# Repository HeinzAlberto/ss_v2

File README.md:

# ss_v2
Soldering Station v2 Projekt

Das Soldering Station v2 Projekt basiert auf dem SolderingStation Projekt: https://github.com/ConnyCola/SolderingStation.
Da dieses Projekt nun schon einige Jahre alt ist und mir ein paar kleine Tweeks wie USB-C input oder User-Buttons fehlen, ist dies somit die inoffizielle Fortsetzung.
Der Code basiert maßgebend auf dem des Originalprojekts. 
Hinzugefügt wurde:
- User-Buttons Funktionen (speichern, abrufen und löschen von selbst festgelegten Temperaturwerten)
- Automatisches Standby, wenn PWM über gewisse Zeit einen Wert nicht überschreitet
- Menü, um obriges einzustellen

Die Schaltung basiert ebenfalls auf dem Originalprojekt, wobei hier einige Änderungen vorgenommen wurden:
- Der uC (Atmega328p) wird direkt integriert.
- Es werden drei programmierbare Nutzer-Buttons hinzufügt, z.B. für voreingestellte Temperaturen oder Standby.
- Über einen Pin kann mit einem Federkontakt der Lötkolben automatisch in den Standy gesetzt werden, wenn er in die Halterung gelegt wird.
- Es gibt nun eine AVR-ISP-Schnittstelle zur Programmierung.
- Der OpAmp wurde durch ein günstigeres Modell ersetzt.
- Es gibt neben dem bisherigen Rundstecker auch einen USB-C Anschluss, der Power Delivery (USB-PD) unterstützt.
- Ein Kippschalter wird eingesetzt, um zwischen Rundstecker und USB-C zu schalten um somit reverse-current zu verhindern.

ToDo:
Der gesamte Programmierteil sowie ein Prüfen der Schaltung.

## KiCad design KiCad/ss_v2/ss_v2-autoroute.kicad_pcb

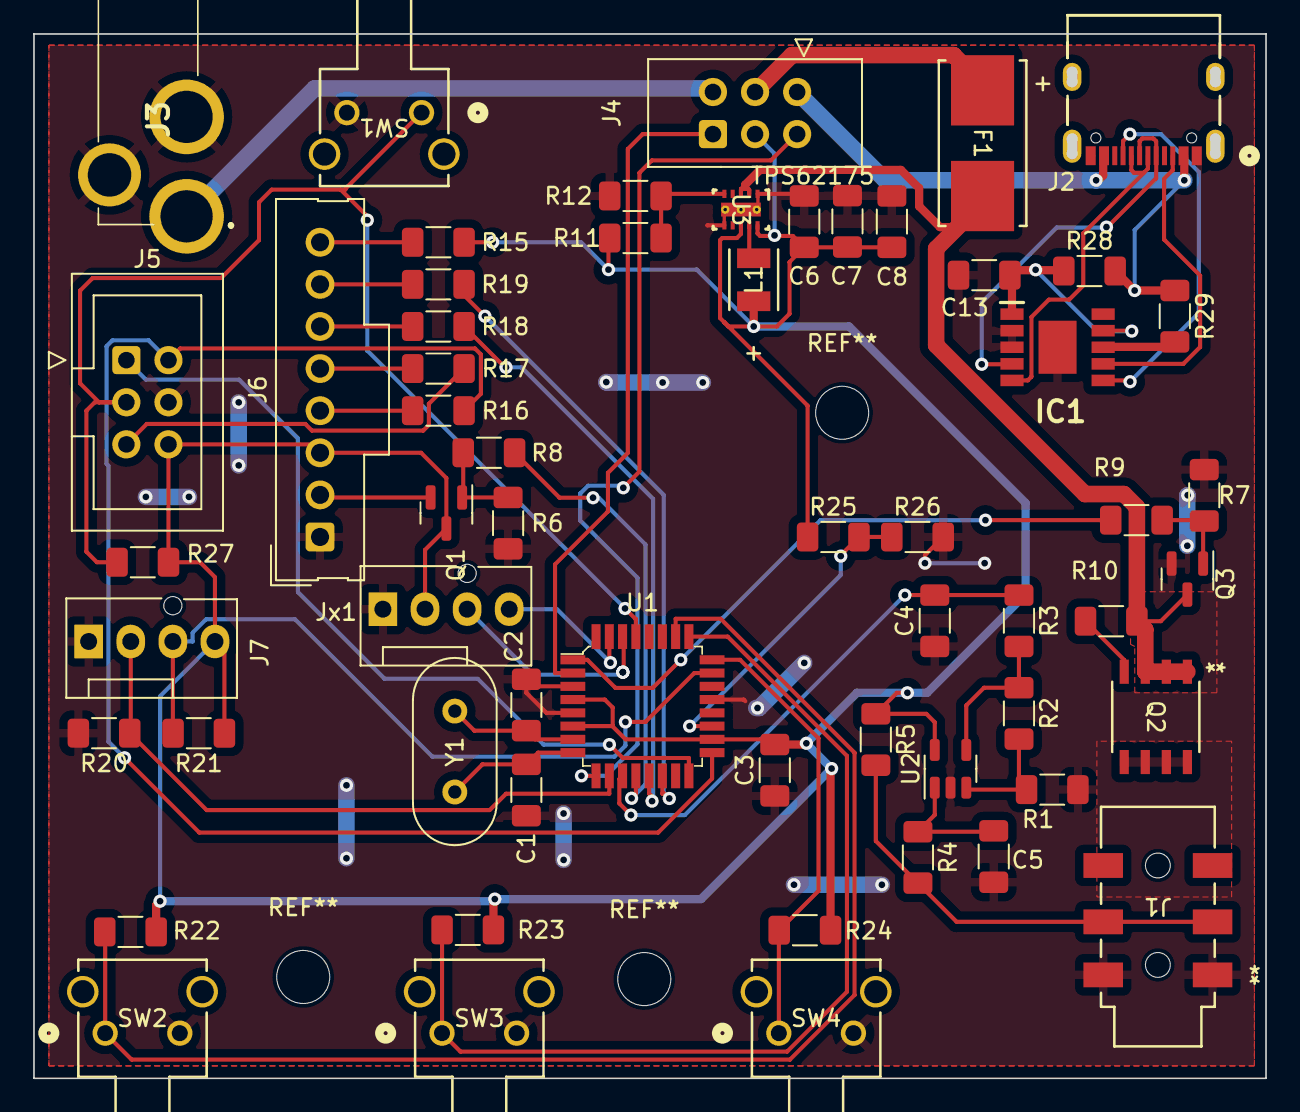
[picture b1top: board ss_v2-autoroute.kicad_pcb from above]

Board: 2 copper layers, 73.8 x 62.5 mm, 58 parts (0 on the bottom side), 47 nets.

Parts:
C1, C2: 22p; R_1206_3216Metric_Pad1.30x1.75mm_HandSolder
C3, C4, C5: 100n; R_1206_3216Metric_Pad1.30x1.75mm_HandSolder
C6, C7, C8: 10u; R_1206_3216Metric_Pad1.30x1.75mm_HandSolder
C13: 1u; R_1206_3216Metric_Pad1.30x1.75mm_HandSolder
F1: 0154003.DR; 0154Series_LTF
IC1: CH224K; SOP100P600X180-11N
J1: PJ-313D-B-SMT; PJ-313D-B-SMT_XKB
J2: GT-USB-7004; CONN12_B-7004_GSW
J3: DC-005-20A; DC00520A
J4: Conn_02x03_Top_Bottom; IDC-Header_2x03_P2.54mm_Vertical
J5: Conn_02x03_Counter_Clockwise; IDC-Header_2x03_P2.54mm_Vertical
J6: Conn_01x08_Pin; Molex_SL_171971-0008_1x08_P2.54mm_Vertical
J7: Conn_01x04; FanPinHeader_1x04_P2.54mm_Vertical
Jx1: Conn_01x04; FanPinHeader_1x04_P2.54mm_Vertical
L1: 10u; IND_NLCV32T_TDK
Q1, Q3: BSN20; SOT-23
Q2: IRF7416TRPBF; SO-8_IRF741_INF
R1: 100k; R_1206_3216Metric_Pad1.30x1.75mm_HandSolder
R2: 56k; R_1206_3216Metric_Pad1.30x1.75mm_HandSolder
R3, R4, R8, R9, R10, R15, R16, R17, R18, R19, R28: 1k; R_1206_3216Metric_Pad1.30x1.75mm_HandSolder
R5, R20: 1M; R_1206_3216Metric_Pad1.30x1.75mm_HandSolder
R6, R7, R21, R22, R23, R24, R25, R26, R27, R29: 10k; R_1206_3216Metric_Pad1.30x1.75mm_HandSolder
R11: 270k; R_1206_3216Metric_Pad1.30x1.75mm_HandSolder
R12: 51k; R_1206_3216Metric_Pad1.30x1.75mm_HandSolder
SW1, SW2, SW3, SW4: TS-1093C-A15; SW_TS-1093C-A15_YDI
U1: ATMEGA328P-AU; TQFP-32_7x7mm
U2: LM321; SOT-23-5
U3: TPS62175DQCR; DQC0010A
Y1: Crystal; Crystal_HC49-U_Vertical

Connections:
+5V: C3.2, C6.2, C7.2, C8.2, J4.5, J5.6, J6.3, J7.4, Jx1.2, L1.1, Q1.3 (D), R5.1, R11.1, R15.1, R21.1, R22.1, R23.1, R24.1, R25.1, R27.1, U1.4 (VCC), U1.6 (VCC), U1.18 (AVCC), U2.5 (V+), U3.8 (SLEEP), U3.10 (VOS)
+12V: J3.1, J4.3
GND: C1.1, C2.1, C3.1, C4.1, C5.1, C6.1, C7.1, C8.1, C13.2, IC1.2 (CFG1), IC1.3 (CFG2), IC1.11 (GND), J1.1A, J1.1B, J2.A1, J2.A12, J2.B1, J2.B12, J3.2, J3.3, J5.4, J6.1, J7.1, Jx1.1, Q3.2 (S), R1.1, R6.1, R7.1, R12.2, R20.2, R26.2, SW1.2, SW2.2, SW3.2, SW4.2, U1.3 (GND), U1.5 (GND), U1.21 (GND), U2.2 (V-), U3.1 (PGND), U3.6 (AGND), U3.11 (PAD)
unnamed: C13.1, IC1.1 (VDD), IC1.9 (CFG3), R28.1
unnamed: IC1.8 (VBUS), R29.2
unnamed: F1.1, J4.2
unnamed: J6.4, R16.2
unnamed: J6.5, R17.2
unnamed: J6.6, R18.2
unnamed: J6.7, R19.2
unnamed: J6.8, R15.2
unnamed: Q1.1 (G), R6.2, R8.2
unnamed: Q2.4 (G), R10.1
unnamed: Q3.1 (G), R7.2, R9.1
unnamed: R2.1, R3.2, U2.4
unnamed: C2.2, U1.7 (PB6), Y1.1
unnamed: C1.2, U1.8 (PB7), Y1.2
unnamed: C5.2, R4.1, U2.1 (+)
unnamed: R1.2, R2.2, U2.3 (-)
unnamed: R11.2, R12.1, U3.5 (FB)
unnamed: L1.2, U3.9 (SW)
VBUS: J2.A4, J2.A9, J2.B4, J2.B9, J4.1, R28.2, R29.1
VDC: F1.2, Q2.1 (S), Q2.2 (S), Q2.3 (S), Q3.3 (D), R10.2, U3.2 (VIN), U3.3 (EN)
analog_in: C4.2, R3.1, U1.11 (PD7)
bl: J6.2, Q1.2 (S)
bl_ctrl: R8.1, U1.12 (PB0)
cc1: IC1.6 (CC1), J2.A5
cc2: IC1.7 (CC2), J2.B5
cs: R19.1, U1.14 (PB2)
dc: R18.1, U1.13 (PB1)
dm: IC1.5 (DM), J2.A7, J2.B7
dp: IC1.4 (DP), J2.A6, J2.B6
miso: J5.1, U1.16 (PB4)
mosi: J5.5, R17.1
output_power: J1.2A, J1.2B, Q2.5 (D), Q2.6 (D), Q2.7 (D), Q2.8 (D)
poti: J7.2, R20.1, U1.10 (PD6)
reset: J5.3, R27.2, SW1.1, U1.29 (PC6)
s_ctrl: R9.2, U1.1 (PD3)
sb: J7.3, R21.2, U1.23 (PC0)
sck: J5.2, R16.1, U1.17 (PB5)
sens: J1.3A, J1.3B, R4.2, R5.2
sense_12v: J4.6, U1.2 (PD4)
sense_usb: J4.4, U1.9 (PD5)
standby: R25.2, R26.1, U1.19 (ADC6)
u1: R22.2, SW2.1, U1.26 (PC3)
u2: R23.2, SW3.1, U1.25 (PC2)
u3: R24.2, SW4.1, U1.24 (PC1)

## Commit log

2023-07-31 Creating Project with KiCad
2023-07-31 Delete KiCad/ss_v2 directory
    weg damit
2023-07-31 Generieren des Projektes
2023-07-31 Erstellen des Schaltplans der Version 1
2023-07-31 Standby pin hinzufeguegt
2023-07-31 korrektur der Fehlenden Footprints
2023-07-31 Anordnen der Bauteile
2023-07-31 BOM hinzugefügt
2023-07-31 Erster Routing Versuch
2023-08-01 Autoroute-Bsp. hinzugefügt. Sollte sogar funktionieren.
2023-08-01 Autorouting verbessert
2023-08-01 Datenlatt für An-/Ausschalter hinzugefügt
2023-08-01 Anpassen des Layouts
2023-08-01 Switch-Conn. angepasst.
2023-08-01 Fertigungsdateien erzeugt inkl. PDF des Schaltplans
2023-08-02 Das ist ein Test, weil etwas nicht funktioniert.
2023-08-02 in ss_v2.1 wurde FUSB302 durch kleineren, einfacheren und günstigeren CH244 ersetzt.
2023-08-02 Schaltplan fertig. Einige Bauteil-Libs fehlen noch / werden nicht richtig erkannt. Das sollte behoben werden bevor das PCB abktualisiert werden kann...
2023-08-12 Versucht, FUSB zu ersetzen. Bin gescheitert, da KiCad genialerweise neue Bauteilnummern vergeben hat und man so jetzt das gessamte Layout neu machen müsste oder alle Nummern einzeln anpassen müsste. 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
2023-08-12 ss_v2 mit neuem Chip umgesetzt. Sieht soweit gut aus, keine Probleme festgestellt. Bitte um Überprüfung.
2023-08-19 GND an 328p gefixt
2024-03-25 Unbenanntes Diagramm.drawio eingefügt
